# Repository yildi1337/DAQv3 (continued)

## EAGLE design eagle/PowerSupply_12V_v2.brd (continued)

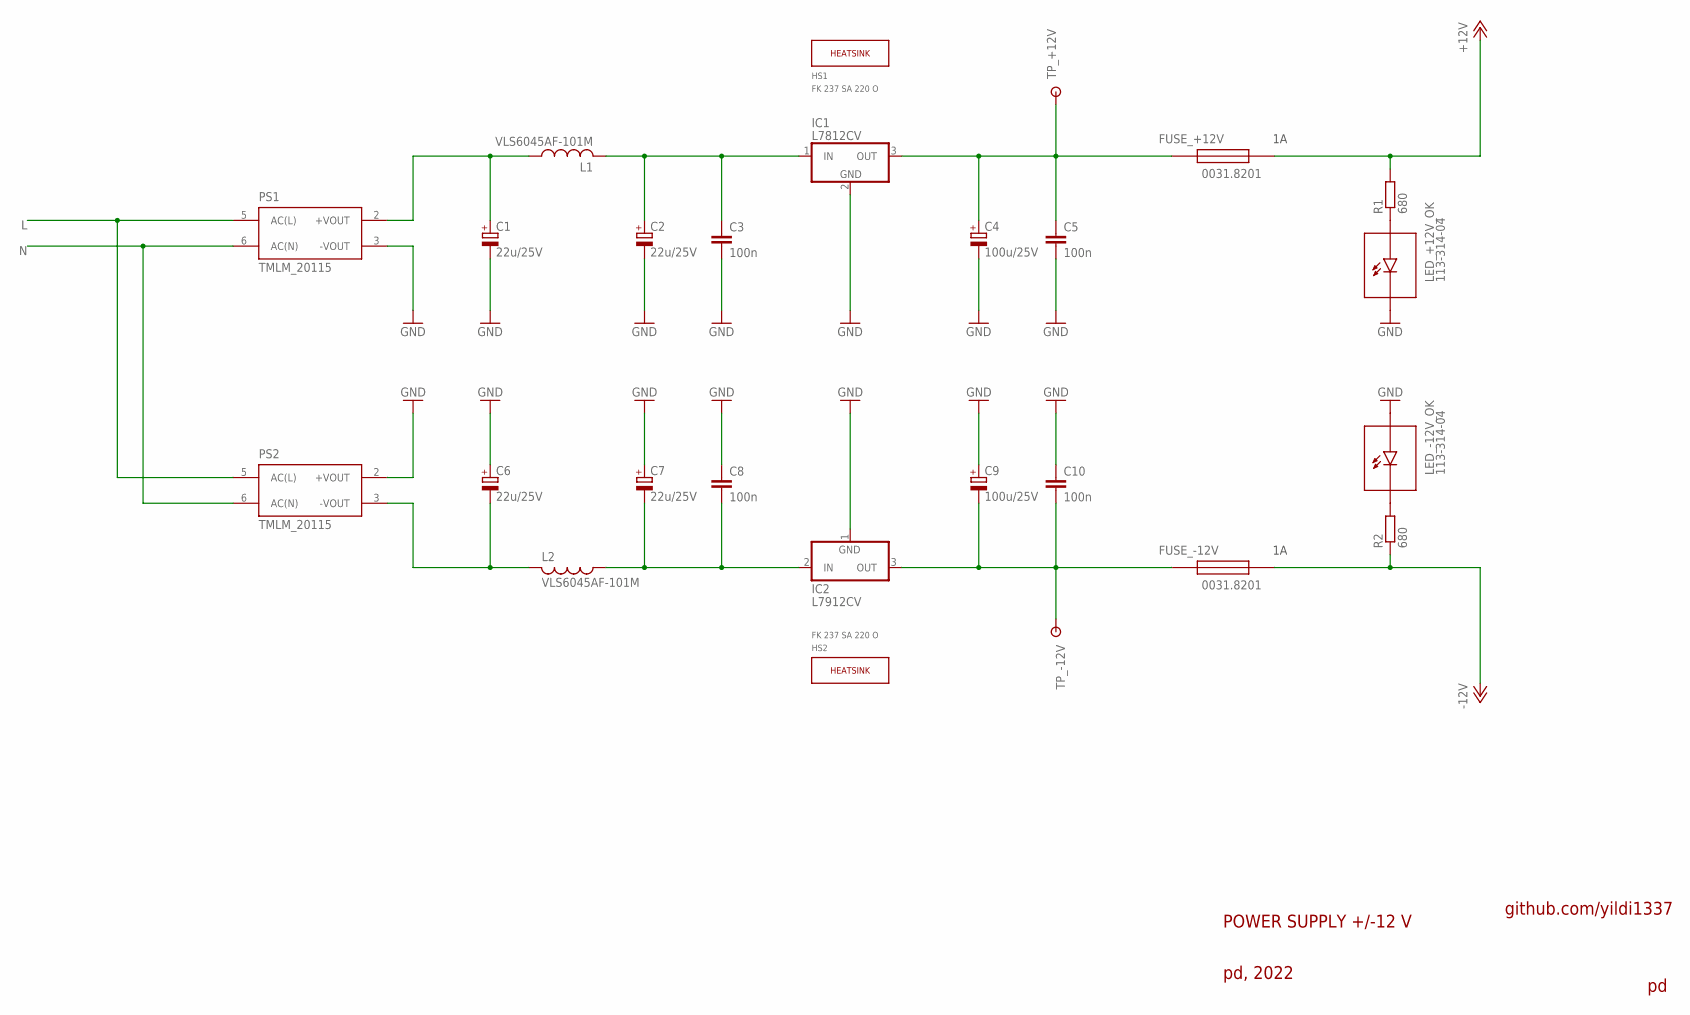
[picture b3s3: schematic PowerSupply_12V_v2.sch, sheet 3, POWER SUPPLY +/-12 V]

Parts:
C1, C2, C6, C7: 22u/25V; 153CLV-0505
C3, C5, C8, C10: 100n; C0603
C4, C9: 100u/25V; 153CLV-0810
FUSE_+12V: 0031.8201
FUSE_-12V: 0031.8201
HS1, HS2: FK 237 SA 220 O; FK_237_SA_220_O
IC1: L7812CV
IC2: L7912CV
L1, L2: VLS6045AF-101M
LED_+12V_OK: 113-314-04
LED_-12V_OK: 113-314-04
PS1, PS2: TMLM_20115; TMLM_201XX
R1, R2: 680; R0603
TP_+12V: RSPRO-1MM-TERMINAL-POST-2622034
TP_-12V: RSPRO-1MM-TERMINAL-POST-2622034

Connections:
+12V: FUSE_+12V.2, R1.2; also elsewhere on the board
-12V: FUSE_-12V.2, R2.1; also elsewhere on the board
GND: C1.-, C2.-, C3.2, C4.-, C5.2, C6.+, C7.+, C8.1, C9.+, C10.1, IC1.2 (GND), IC2.1 (GND), LED_+12V_OK.- (C), LED_-12V_OK.+ (A), PS1.3 (-VOUT), PS2.2 (+VOUT); also elsewhere on the board
L: PS1.5 (AC(L)), PS2.5 (AC(L)); also elsewhere on the board
N: PS1.6 (AC(N)), PS2.6 (AC(N)); also elsewhere on the board
unnamed: C7.-, C8.2, IC2.2 (IN), L2.1
unnamed: LED_-12V_OK.- (C), R2.2
unnamed: C9.-, C10.2, FUSE_-12V.1, IC2.3 (OUT), TP_-12V.P$1
unnamed: C1.+, L1.1, PS1.2 (+VOUT)
unnamed: C6.-, L2.2, PS2.3 (-VOUT)
unnamed: LED_+12V_OK.+ (A), R1.1
unnamed: C4.+, C5.1, FUSE_+12V.1, IC1.3 (OUT), TP_+12V.P$1
unnamed: C2.+, C3.1, IC1.1 (IN), L1.2

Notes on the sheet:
POWER SUPPLY +/-12 V
pd, 2022
github.com/yildi1337

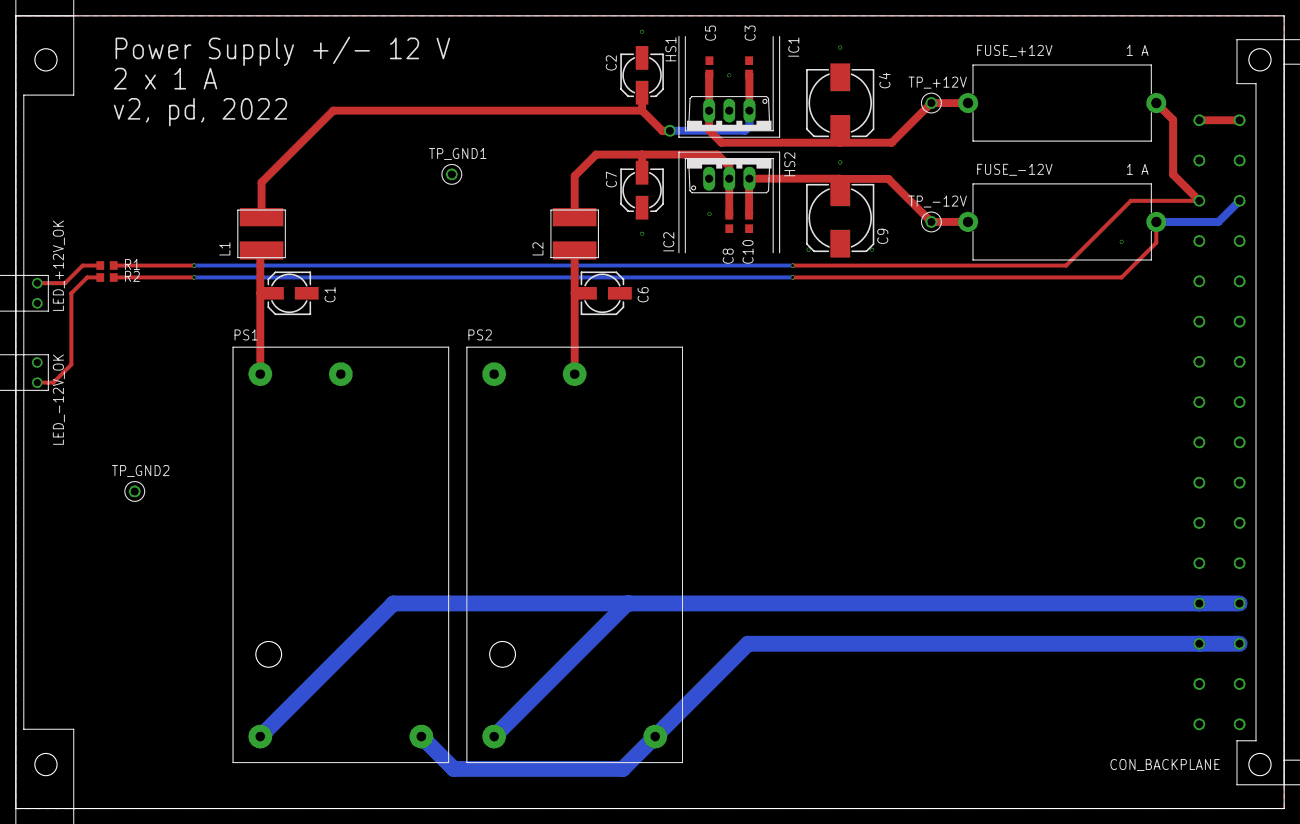
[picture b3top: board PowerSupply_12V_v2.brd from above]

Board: 2 copper layers, 160.0 x 100.0 mm, 30 parts (0 on the bottom side), 14 nets.

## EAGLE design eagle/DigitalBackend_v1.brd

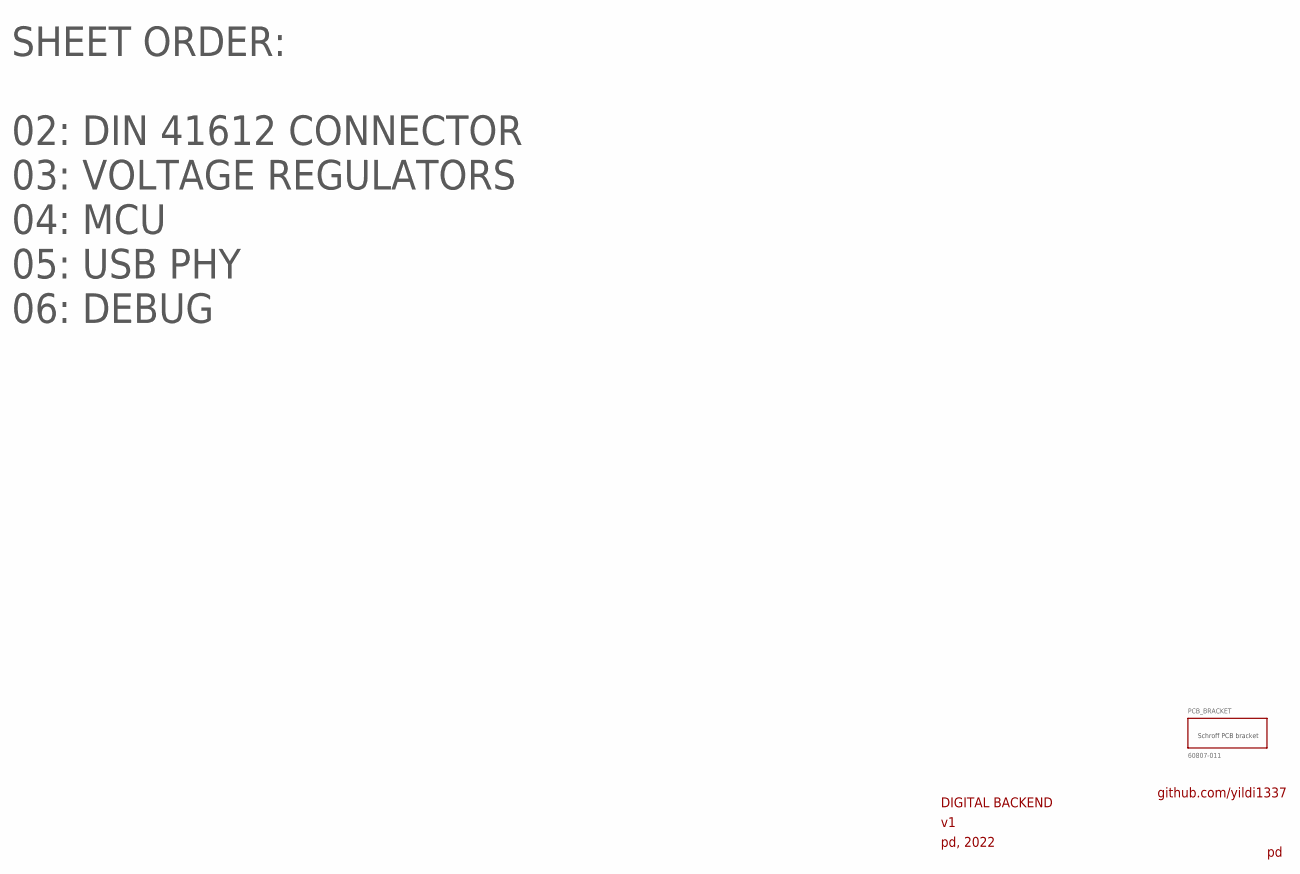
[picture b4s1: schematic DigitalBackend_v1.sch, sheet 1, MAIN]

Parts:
PCB_BRACKET: 60807-011

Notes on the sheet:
DIGITAL BACKEND
pd, 2022
github.com/yildi1337
SHEET ORDER: 02: DIN 41612 CONNECTOR 03: VOLTAGE REGULATORS 04: MCU 05: USB PHY 06: DEBUG

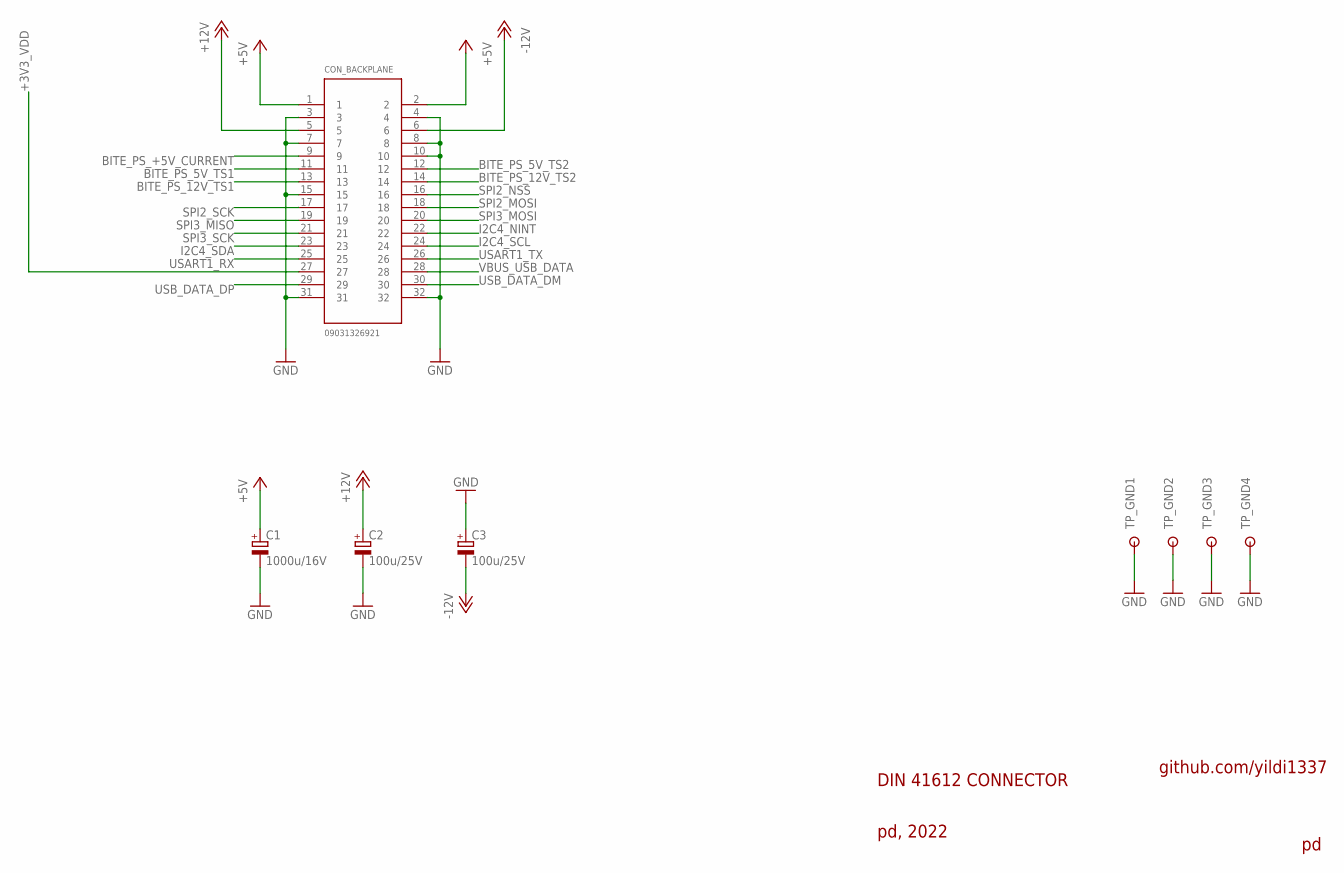
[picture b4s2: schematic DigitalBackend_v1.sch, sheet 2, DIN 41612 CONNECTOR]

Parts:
C1: 1000u/16V; 153CLV-1010
C2, C3: 100u/25V; 153CLV-0810
CON_BACKPLANE: 09031326921
TP_GND1, TP_GND2, TP_GND3, TP_GND4: RSPRO-1MM-TERMINAL-POST-2622034

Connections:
+3V3_VDD: CON_BACKPLANE.27; also elsewhere on the board
+5V: C1.+, CON_BACKPLANE.1, CON_BACKPLANE.2; also elsewhere on the board
+12V: C2.+, CON_BACKPLANE.5; also elsewhere on the board
-12V: C3.-, CON_BACKPLANE.6
BITE_PS_5V_TS1: CON_BACKPLANE.11
BITE_PS_5V_TS2: CON_BACKPLANE.12
BITE_PS_12V_TS1: CON_BACKPLANE.13
BITE_PS_12V_TS2: CON_BACKPLANE.14
BITE_PS_+5V_CURRENT: CON_BACKPLANE.9
GND: C1.-, C2.-, C3.+, CON_BACKPLANE.3, CON_BACKPLANE.4, CON_BACKPLANE.7, CON_BACKPLANE.8, CON_BACKPLANE.10, CON_BACKPLANE.15, CON_BACKPLANE.31, CON_BACKPLANE.32, TP_GND1.P$1, TP_GND2.P$1, TP_GND3.P$1, TP_GND4.P$1; also elsewhere on the board
I2C4_NINT: CON_BACKPLANE.22; also elsewhere on the board
I2C4_SCL: CON_BACKPLANE.24; also elsewhere on the board
I2C4_SDA: CON_BACKPLANE.23; also elsewhere on the board
SPI2_MOSI: CON_BACKPLANE.18; also elsewhere on the board
SPI2_NSS: CON_BACKPLANE.16; also elsewhere on the board
SPI2_SCK: CON_BACKPLANE.17; also elsewhere on the board
SPI3_MISO: CON_BACKPLANE.19; also elsewhere on the board
SPI3_MOSI: CON_BACKPLANE.20; also elsewhere on the board
SPI3_SCK: CON_BACKPLANE.21; also elsewhere on the board
USART1_RX: CON_BACKPLANE.25; also elsewhere on the board
USART1_TX: CON_BACKPLANE.26; also elsewhere on the board
USB_DATA_DM: CON_BACKPLANE.30; also elsewhere on the board
USB_DATA_DP: CON_BACKPLANE.29; also elsewhere on the board
VBUS_USB_DATA: CON_BACKPLANE.28; also elsewhere on the board

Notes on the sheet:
DIN 41612 CONNECTOR
pd, 2022
github.com/yildi1337

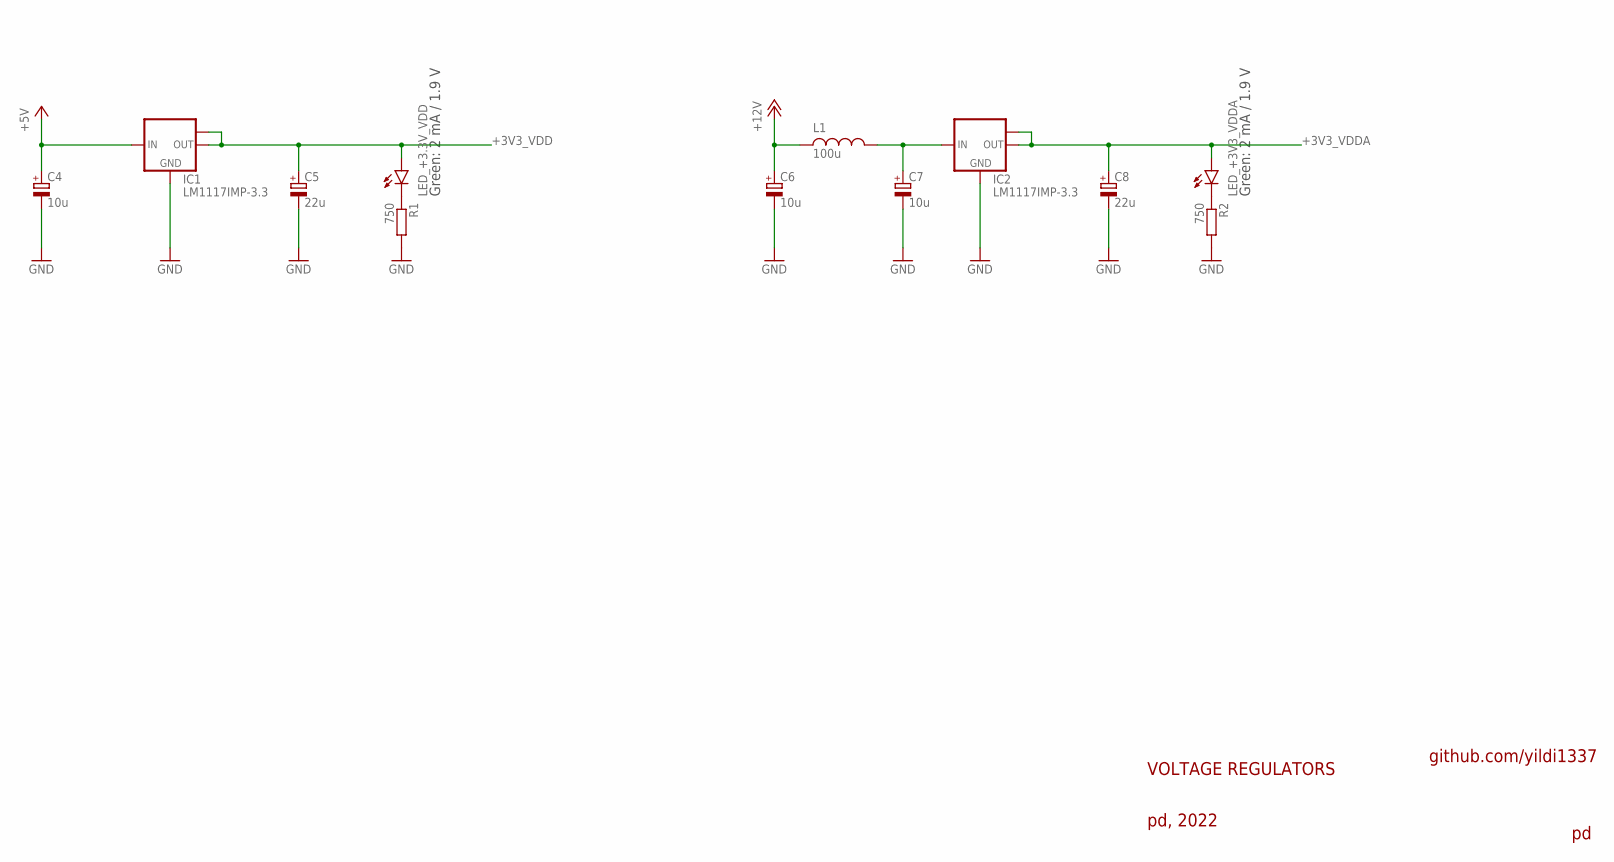
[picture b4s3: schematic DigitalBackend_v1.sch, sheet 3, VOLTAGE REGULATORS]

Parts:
C4, C6, C7: 10u; CT3216
C5, C8: 22u; CT6032
IC1, IC2: LM1117IMP-3.3; SOT223
L1: 100u; VLS6045AF-101M
LED_+3.3V_VDD, LED_+3V3_VDDA: LEDCHIP-LED0603; CHIP-LED0603
R1, R2: 750; R0603

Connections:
+3V3_VDD: C5.+, IC1.2 (OUT), IC1.TAB (OUT1), LED_+3.3V_VDD.A; also elsewhere on the board
+3V3_VDDA: C8.+, IC2.2 (OUT), IC2.TAB (OUT1), LED_+3V3_VDDA.A; also elsewhere on the board
+5V: C4.+, IC1.3 (IN); also elsewhere on the board
+12V: C6.+, L1.1; also elsewhere on the board
GND: C4.-, C5.-, C6.-, C7.-, C8.-, IC1.1 (GND), IC2.1 (GND), R1.2, R2.2; also elsewhere on the board
unnamed: C7.+, IC2.3 (IN), L1.2
unnamed: LED_+3.3V_VDD.C, R1.1
unnamed: LED_+3V3_VDDA.C, R2.1

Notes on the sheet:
VOLTAGE REGULATORS
pd, 2022
github.com/yildi1337
Green: 2 mA / 1.9 V

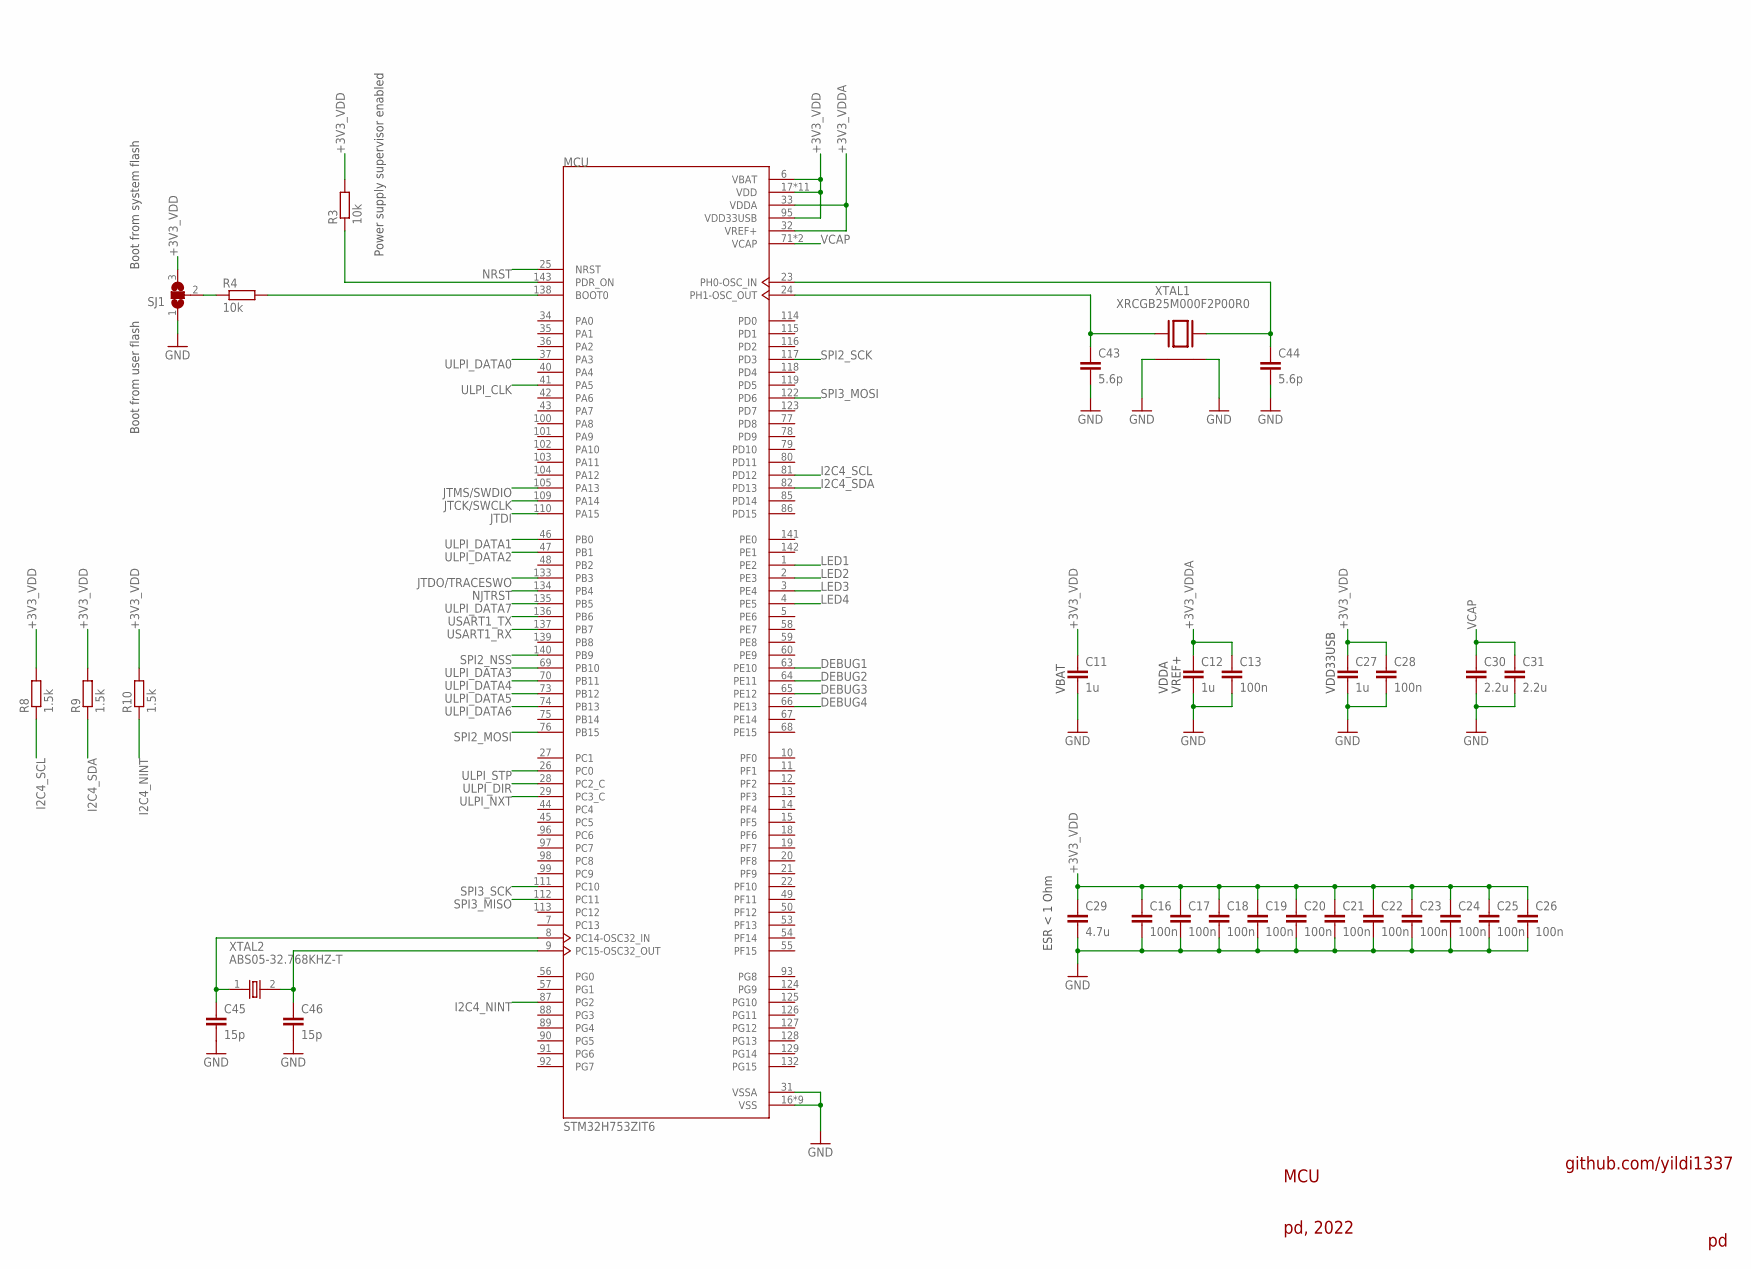
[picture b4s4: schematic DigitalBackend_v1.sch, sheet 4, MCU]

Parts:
C11, C12, C27: 1u; C0603
C13, C16, C17, C18, C19, C20, C21, C22, C23, C24, C25, C26, C28: 100n; C0603
C29: 4.7u; C0603
C30, C31: 2.2u; C0603
C43, C44: 5.6p; C0603
C45, C46: 15p; C0603
MCU: STM32H753ZIT6; LQFP144
R3, R4: 10k; R0603
R8, R9, R10: 1.5k; R0603
SJ1: SJ2W; SJ_2
XTAL1: XRCGB25M000F2P00R0
XTAL2: ABS05-32.768KHZ-T

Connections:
+3V3_VDD: C11.1, C16.1, C17.1, C18.1, C19.1, C20.1, C21.1, C22.1, C23.1, C24.1, C25.1, C26.1, C27.1, C28.1, C29.1, MCU.6 (VBAT), MCU.17 (VDD), MCU.30 (VDD), MCU.39 (VDD), MCU.52 (VDD), MCU.62 (VDD), MCU.72 (VDD), MCU.84 (VDD), MCU.95 (VDD33USB), MCU.108 (VDD), MCU.121 (VDD), MCU.131 (VDD), MCU.144 (VDD), R3.2, R8.2, R9.2, R10.2, SJ1.3; also elsewhere on the board
+3V3_VDDA: C12.1, C13.1, MCU.32 (VREF+), MCU.33 (VDDA); also elsewhere on the board
DEBUG1: MCU.63 (PE10); also elsewhere on the board
DEBUG2: MCU.64 (PE11); also elsewhere on the board
DEBUG3: MCU.65 (PE12); also elsewhere on the board
DEBUG4: MCU.66 (PE13); also elsewhere on the board
GND: C11.2, C12.2, C13.2, C16.2, C17.2, C18.2, C19.2, C20.2, C21.2, C22.2, C23.2, C24.2, C25.2, C26.2, C27.2, C28.2, C29.2, C30.2, C31.2, C43.2, C44.2, C45.2, C46.2, MCU.16 (VSS), MCU.31 (VSSA), MCU.38 (VSS), MCU.51 (VSS), MCU.61 (VSS), MCU.83 (VSS), MCU.94 (VSS), MCU.107 (VSS), MCU.120 (VSS), MCU.130 (VSS), SJ1.1, XTAL1.2 (GND2), XTAL1.4 (GND4); also elsewhere on the board
I2C4_NINT: MCU.87 (PG2), R10.1; also elsewhere on the board
I2C4_SCL: MCU.81 (PD12), R8.1; also elsewhere on the board
I2C4_SDA: MCU.82 (PD13), R9.1; also elsewhere on the board
JTCK/SWCLK: MCU.109 (PA14); also elsewhere on the board
JTDI: MCU.110 (PA15); also elsewhere on the board
JTDO/TRACESWO: MCU.133 (PB3); also elsewhere on the board
JTMS/SWDIO: MCU.105 (PA13); also elsewhere on the board
LED1: MCU.1 (PE2); also elsewhere on the board
LED2: MCU.2 (PE3); also elsewhere on the board
LED3: MCU.3 (PE4); also elsewhere on the board
LED4: MCU.4 (PE5); also elsewhere on the board
unnamed: MCU.143 (PDR_ON), R3.1
unnamed: MCU.138 (BOOT0), R4.2
unnamed: R4.1, SJ1.2
unnamed: C45.1, MCU.8 (PC14-OSC32_IN), XTAL2.1
unnamed: C44.1, MCU.23 (PH0-OSC_IN), XTAL1.3
unnamed: C43.1, MCU.24 (PH1-OSC_OUT), XTAL1.1
unnamed: C46.1, MCU.9 (PC15-OSC32_OUT), XTAL2.2
NJTRST: MCU.134 (PB4); also elsewhere on the board
NRST: MCU.25 (NRST); also elsewhere on the board
SPI2_MOSI: MCU.76 (PB15); also elsewhere on the board
SPI2_NSS: MCU.140 (PB9); also elsewhere on the board
SPI2_SCK: MCU.117 (PD3); also elsewhere on the board
SPI3_MISO: MCU.112 (PC11); also elsewhere on the board
SPI3_MOSI: MCU.122 (PD6); also elsewhere on the board
SPI3_SCK: MCU.111 (PC10); also elsewhere on the board
ULPI_CLK: MCU.41 (PA5); also elsewhere on the board
ULPI_DATA0: MCU.37 (PA3); also elsewhere on the board
ULPI_DATA1: MCU.46 (PB0); also elsewhere on the board
ULPI_DATA2: MCU.47 (PB1); also elsewhere on the board
ULPI_DATA3: MCU.69 (PB10); also elsewhere on the board
ULPI_DATA4: MCU.70 (PB11); also elsewhere on the board
ULPI_DATA5: MCU.73 (PB12); also elsewhere on the board
ULPI_DATA6: MCU.74 (PB13); also elsewhere on the board
ULPI_DATA7: MCU.135 (PB5); also elsewhere on the board
ULPI_DIR: MCU.28 (PC2_C); also elsewhere on the board
ULPI_NXT: MCU.29 (PC3_C); also elsewhere on the board
ULPI_STP: MCU.26 (PC0); also elsewhere on the board
USART1_RX: MCU.137 (PB7); also elsewhere on the board
USART1_TX: MCU.136 (PB6); also elsewhere on the board
VCAP: C30.1, C31.1, MCU.71 (VCAP), MCU.106 (VCAP)

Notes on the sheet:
MCU
pd, 2022
github.com/yildi1337
ESR < 1 Ohm
Power supply supervisor enabled
Boot from user flash
Boot from system flash
VBAT
VDDA
VDD33USB
VREF+

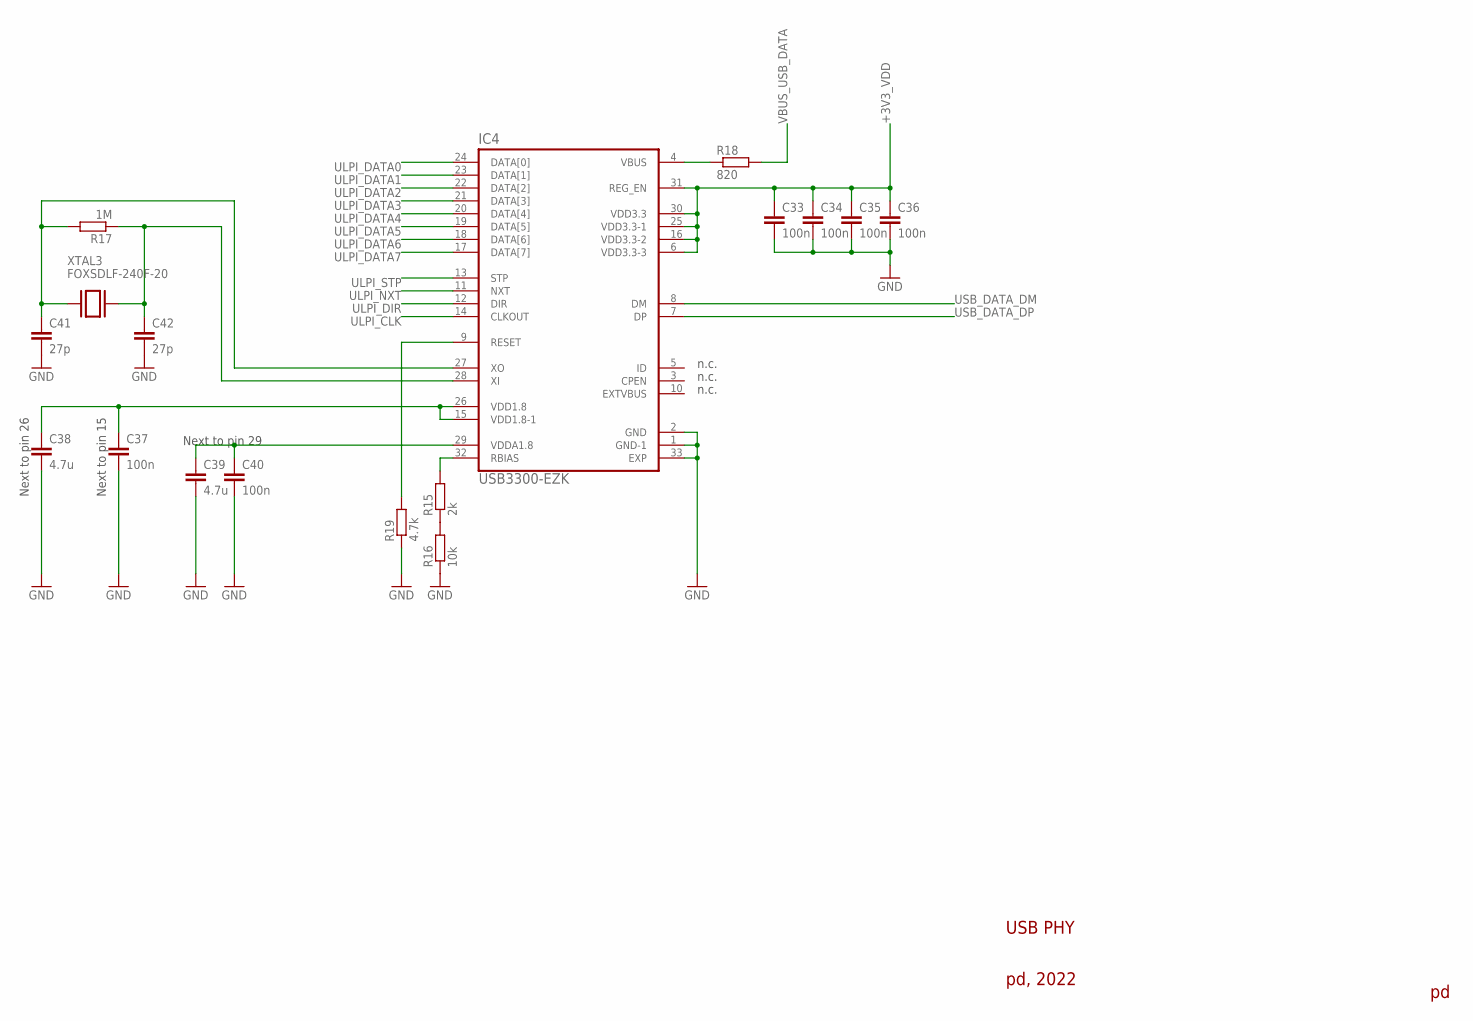
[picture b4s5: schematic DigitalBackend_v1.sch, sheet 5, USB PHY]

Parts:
C33, C34, C35, C36, C37, C40: 100n; C0603
C38, C39: 4.7u; C0603
C41, C42: 27p; C0603
IC4: USB3300-EZK
R15: 2k; R0603
R16: 10k; R0603
R17: 1M; R0603
R18: 820; R0603
R19: 4.7k; R0603
XTAL3: FOXSDLF-240F-20

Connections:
+3V3_VDD: C33.1, C34.1, C35.1, C36.1, IC4.6 (VDD3.3-3), IC4.16 (VDD3.3-2), IC4.25 (VDD3.3-1), IC4.30 (VDD3.3), IC4.31 (REG_EN); also elsewhere on the board
GND: C33.2, C34.2, C35.2, C36.2, C37.2, C38.2, C39.2, C40.2, C41.2, C42.2, IC4.1 (GND-1), IC4.2 (GND), IC4.33 (EXP), R16.1, R19.1; also elsewhere on the board
unnamed: C37.1, C38.1, IC4.15 (VDD1.8-1), IC4.26 (VDD1.8)
unnamed: C39.1, C40.1, IC4.29 (VDDA1.8)
unnamed: R15.1, R16.2
unnamed: IC4.32 (RBIAS), R15.2
unnamed: C41.1, IC4.27 (XO), R17.2, XTAL3.1
unnamed: C42.1, IC4.28 (XI), R17.1, XTAL3.2
unnamed: IC4.4 (VBUS), R18.1
unnamed: IC4.9 (RESET), R19.2
ULPI_CLK: IC4.14 (CLKOUT); also elsewhere on the board
ULPI_DATA0: IC4.24 (DATA[0]); also elsewhere on the board
ULPI_DATA1: IC4.23 (DATA[1]); also elsewhere on the board
ULPI_DATA2: IC4.22 (DATA[2]); also elsewhere on the board
ULPI_DATA3: IC4.21 (DATA[3]); also elsewhere on the board
ULPI_DATA4: IC4.20 (DATA[4]); also elsewhere on the board
ULPI_DATA5: IC4.19 (DATA[5]); also elsewhere on the board
ULPI_DATA6: IC4.18 (DATA[6]); also elsewhere on the board
ULPI_DATA7: IC4.17 (DATA[7]); also elsewhere on the board
ULPI_DIR: IC4.12 (DIR); also elsewhere on the board
ULPI_NXT: IC4.11 (NXT); also elsewhere on the board
ULPI_STP: IC4.13 (STP); also elsewhere on the board
USB_DATA_DM: IC4.8 (DM); also elsewhere on the board
USB_DATA_DP: IC4.7 (DP); also elsewhere on the board
VBUS_USB_DATA: R18.2; also elsewhere on the board

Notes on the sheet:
USB PHY
pd, 2022
n.c.
Next to pin 26
Next to pin 15
Next to pin 29

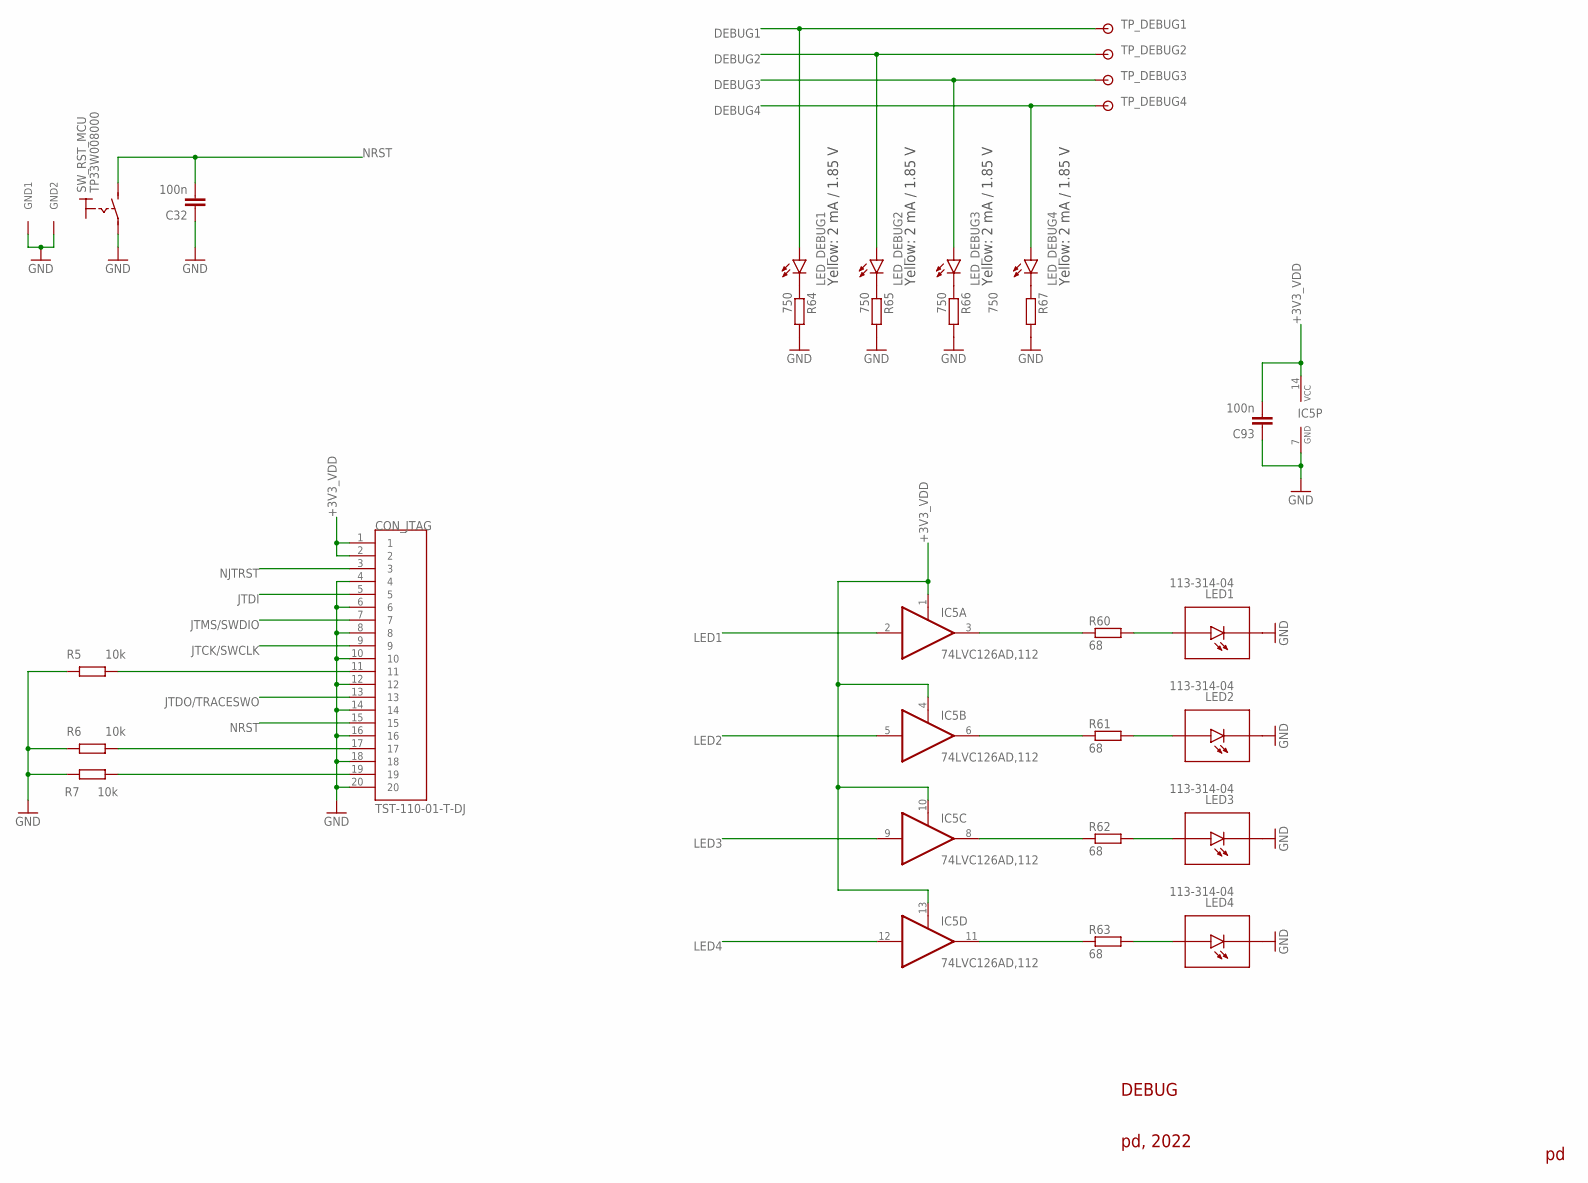
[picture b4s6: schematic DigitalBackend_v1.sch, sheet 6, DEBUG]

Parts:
C32, C93: 100n; C0603
CON_JTAG: TST-110-01-T-DJ; TST-110-01-T-D
IC5: 74LVC126AD,112; SO14
LED1, LED2, LED3, LED4: 113-314-04
LED_DEBUG1, LED_DEBUG2, LED_DEBUG3, LED_DEBUG4: LEDCHIP-LED0603; CHIP-LED0603
R5, R6, R7: 10k; R0603
R60, R61, R62, R63: 68; R0603
R64, R65, R66, R67: 750; R0603
SW_RST_MCU: TP33W008000
TP_DEBUG1, TP_DEBUG2, TP_DEBUG3, TP_DEBUG4: RSPRO-1MM-TERMINAL-POST-2622034

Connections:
+3V3_VDD: C93.2, CON_JTAG.1, CON_JTAG.2, IC5.1 (OE), IC5.4 (OE), IC5.10 (OE), IC5.13 (OE), IC5.14 (VCC); also elsewhere on the board
DEBUG1: LED_DEBUG1.A, TP_DEBUG1.P$1; also elsewhere on the board
DEBUG2: LED_DEBUG2.A, TP_DEBUG2.P$1; also elsewhere on the board
DEBUG3: LED_DEBUG3.A, TP_DEBUG3.P$1; also elsewhere on the board
DEBUG4: LED_DEBUG4.A, TP_DEBUG4.P$1; also elsewhere on the board
GND: C32.1, C93.1, CON_JTAG.4, CON_JTAG.6, CON_JTAG.8, CON_JTAG.10, CON_JTAG.12, CON_JTAG.14, CON_JTAG.16, CON_JTAG.18, CON_JTAG.20, IC5.7 (GND), LED1.- (C), LED2.- (C), LED3.- (C), LED4.- (C), R5.1, R6.1, R7.1, R64.2, R65.2, R66.2, R67.2, SW_RST_MCU.GND1, SW_RST_MCU.GND2, SW_RST_MCU.P1; also elsewhere on the board
JTCK/SWCLK: CON_JTAG.9; also elsewhere on the board
JTDI: CON_JTAG.5; also elsewhere on the board
JTDO/TRACESWO: CON_JTAG.13; also elsewhere on the board
JTMS/SWDIO: CON_JTAG.7; also elsewhere on the board
LED1: IC5.2 (I); also elsewhere on the board
LED2: IC5.5 (I); also elsewhere on the board
LED3: IC5.9 (I); also elsewhere on the board
LED4: IC5.12 (I); also elsewhere on the board
unnamed: CON_JTAG.19, R7.2
unnamed: CON_JTAG.17, R6.2
unnamed: CON_JTAG.11, R5.2
unnamed: LED1.+ (A), R60.2
unnamed: LED2.+ (A), R61.2
unnamed: LED3.+ (A), R62.2
unnamed: LED4.+ (A), R63.2
unnamed: IC5.3 (O), R60.1
unnamed: IC5.6 (O), R61.1
unnamed: IC5.8 (O), R62.1
unnamed: IC5.11 (O), R63.1
unnamed: LED_DEBUG1.C, R64.1
unnamed: LED_DEBUG2.C, R65.1
unnamed: LED_DEBUG3.C, R66.1
unnamed: LED_DEBUG4.C, R67.1
NJTRST: CON_JTAG.3; also elsewhere on the board
NRST: C32.2, CON_JTAG.15, SW_RST_MCU.P3; also elsewhere on the board

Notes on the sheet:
DEBUG
pd, 2022
Yellow: 2 mA / 1.85 V

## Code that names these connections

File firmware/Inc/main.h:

/*
 *******************************************************************************
 * File:			main.h
 * Date:			2022-04-10
 * Author:			Phillip Durdaut
 * Summary:			Main include file with main program definitions
 * Notes:			-
 *******************************************************************************
 */

/* Define to prevent recursive inclusion -------------------------------------*/
#ifndef __MAIN_H
#define __MAIN_H

/* Includes ------------------------------------------------------------------*/
#include <stdio.h>
#include <stdlib.h>
#include <string.h>
#include <stdbool.h>
#include <stdint.h>
#include <float.h>
#include <ctype.h>

#include "stm32h7xx.h"
#include "stm32h7xx_hal.h"
#include "stm32h7xx_it.h"

#include "tca9534a.h"

/* Public defines ------------------------------------------------------------*/

/* ADC */
#define MAIN_ADC_SAMPLES_PER_SECOND						256e3
#define MAIN_ADC_SAMPLES_PER_MILLI_SECOND				256
#define MAIN_ADC_NUM_CHANNELS							4
#define MAIN_ADC_BYTES_PER_SAMPLE_PER_CHANNEL			4
#define MAIN_ADC_BYTES_PER_SAMPLE						(MAIN_ADC_NUM_CHANNELS * MAIN_ADC_BYTES_PER_SAMPLE_PER_CHANNEL)
#define MAIN_ADC_BYTES_PER_SECOND_PER_CHANNEL			(MAIN_ADC_BYTES_PER_SAMPLE_PER_CHANNEL * MAIN_ADC_SAMPLES_PER_SECOND)
#define MAIN_ADC_BYTES_PER_SECOND						(MAIN_ADC_NUM_CHANNELS * MAIN_ADC_BYTES_PER_SAMPLE_PER_CHANNEL * MAIN_ADC_SAMPLES_PER_SECOND)
#define MAIN_ADC_BYTES_PER_MILLI_SECOND_PER_CHANNEL		(MAIN_ADC_BYTES_PER_SAMPLE_PER_CHANNEL * MAIN_ADC_SAMPLES_PER_MILLI_SECOND)
#define MAIN_ADC_BYTES_PER_MILLI_SECOND					(MAIN_ADC_NUM_CHANNELS * MAIN_ADC_BYTES_PER_SAMPLE_PER_CHANNEL * MAIN_ADC_SAMPLES_PER_MILLI_SECOND)
#define MAIN_ADC_CLIPPING_VALUE							(4194304+100000)	/* slightly above 2.5 V */

/* USB */
#define MAIN_USB_VENDOR_ID								0x1337
#define MAIN_USB_PRODUCT_ID								0x0011
#define MAIN_USB_LANG_ID_STRING_US		 				0x0409
#define MAIN_USB_LANG_ID_STRING_DE		 				0x0407
#define MAIN_USB_LANG_ID_STRING							MAIN_USB_LANG_ID_STRING_US
#define MAIN_USB_MANUFACTURER_STRING	  				"pd"
#define MAIN_USB_PRODUCT_STRING							"DAQ v3"
#define MAIN_USB_SERIAL_STRING	 						"0000"
#define MAIN_USB_CONFIGURATION_STRING  					"DAQ v3 Config"
#define MAIN_USB_INTERFACE_STRING	  					"DAQ v3 Interface"
#define MAIN_USB_DEVICE_VERSION							0x0100

/* Interrupt priorities */
#define IRQ_UART1_PREEMPT_PRIORITY				2
#define IRQ_UART1_SUB_PRIORITY					2
#define IRQ_DMA1_STREAM0_PREEMPT_PRIORITY		10
#define IRQ_DMA1_STREAM0_SUB_PRIORITY			10
#define IRQ_OTG_HS_EP1_OUT_PREEMPT_PRIORITY		5
#define IRQ_OTG_HS_EP1_OUT_SUB_PRIORITY			5
#define IRQ_OTG_HS_EP1_IN_PREEMPT_PRIORITY		5
#define IRQ_OTG_HS_EP1_IN_SUB_PRIORITY			5
#define IRQ_OTG_HS_PREEMPT_PRIORITY				5
#define IRQ_OTG_HS_SUB_PRIORITY					5

/* Pins and ports */
#define LED_1_Pin 											GPIO_PIN_2
#define LED_1_Port 											GPIOE
#define LED_2_Pin 											GPIO_PIN_3
#define LED_2_Port 											GPIOE
#define LED_3_Pin 											GPIO_PIN_4
#define LED_3_Port 											GPIOE
#define LED_4_Pin 											GPIO_PIN_5
#define LED_4_Port 											GPIOE

#define DEBUG_1_Pin 										GPIO_PIN_10
#define DEBUG_1_Port 										GPIOE
#define DEBUG_2_Pin 										GPIO_PIN_11
#define DEBUG_2_Port 										GPIOE
#define DEBUG_3_Pin 										GPIO_PIN_12
#define DEBUG_3_Port 										GPIOE
#define DEBUG_4_Pin 										GPIO_PIN_13
#define DEBUG_4_Port 										GPIOE

#define UART1_TX_Pin										GPIO_PIN_6
#define UART1_TX_Port 										GPIOB
#define UART1_TX_AF 										GPIO_AF7_USART1
#define UART1_RX_Pin										GPIO_PIN_7
#define UART1_RX_Port 										GPIOB
#define UART1_RX_AF 										GPIO_AF7_USART1

#define SPI2_NSS_Pin 										GPIO_PIN_9
#define SPI2_NSS_Port 										GPIOB
#define SPI2_NSS_AF											GPIO_AF5_SPI2
#define SPI2_SCK_Pin 										GPIO_PIN_3
#define SPI2_SCK_Port 										GPIOD
#define SPI2_SCK_AF											GPIO_AF5_SPI2
#define SPI2_MOSI_Pin 										GPIO_PIN_15
#define SPI2_MOSI_Port 										GPIOB
#define SPI2_MOSI_AF										GPIO_AF5_SPI2

#define SPI3_SCK_Pin 										GPIO_PIN_10
#define SPI3_SCK_Port 										GPIOC
#define SPI3_SCK_AF											GPIO_AF6_SPI3
#define SPI3_MISO_Pin 										GPIO_PIN_11
#define SPI3_MISO_Port 										GPIOC
#define SPI3_MISO_AF										GPIO_AF6_SPI3
#define SPI3_MOSI_Pin 										GPIO_PIN_6
#define SPI3_MOSI_Port 										GPIOD
#define SPI3_MOSI_AF										GPIO_AF5_SPI3

#define USB_OTG_HS_ULPI_STP_Pin 							GPIO_PIN_0
#define USB_OTG_HS_ULPI_STP_Port 							GPIOC
#define USB_OTG_HS_ULPI_STP_AF								GPIO_AF10_OTG2_HS
#define USB_OTG_HS_ULPI_DIR_Pin 							GPIO_PIN_2
#define USB_OTG_HS_ULPI_DIR_Port 							GPIOC
#define USB_OTG_HS_ULPI_DIR_AF								GPIO_AF10_OTG2_HS
#define USB_OTG_HS_ULPI_NXT_Pin 							GPIO_PIN_3
#define USB_OTG_HS_ULPI_NXT_Port 							GPIOC
#define USB_OTG_HS_ULPI_NXT_AF								GPIO_AF10_OTG2_HS
#define USB_OTG_HS_ULPI_CK_Pin 								GPIO_PIN_5
#define USB_OTG_HS_ULPI_CK_Port 							GPIOA
#define USB_OTG_HS_ULPI_CK_AF								GPIO_AF10_OTG2_HS
#define USB_OTG_HS_ULPI_D0_Pin 								GPIO_PIN_3
#define USB_OTG_HS_ULPI_D0_Port 							GPIOA
#define USB_OTG_HS_ULPI_D0_AF								GPIO_AF10_OTG2_HS
#define USB_OTG_HS_ULPI_D1_Pin 								GPIO_PIN_0
#define USB_OTG_HS_ULPI_D1_Port 							GPIOB
#define USB_OTG_HS_ULPI_D1_AF								GPIO_AF10_OTG2_HS
#define USB_OTG_HS_ULPI_D2_Pin 								GPIO_PIN_1
#define USB_OTG_HS_ULPI_D2_Port 							GPIOB
#define USB_OTG_HS_ULPI_D2_AF								GPIO_AF10_OTG2_HS
#define USB_OTG_HS_ULPI_D3_Pin 								GPIO_PIN_10
#define USB_OTG_HS_ULPI_D3_Port 							GPIOB
#define USB_OTG_HS_ULPI_D3_AF								GPIO_AF10_OTG2_HS
#define USB_OTG_HS_ULPI_D4_Pin 								GPIO_PIN_11
#define USB_OTG_HS_ULPI_D4_Port 							GPIOB
#define USB_OTG_HS_ULPI_D4_AF								GPIO_AF10_OTG2_HS
#define USB_OTG_HS_ULPI_D5_Pin 								GPIO_PIN_12
#define USB_OTG_HS_ULPI_D5_Port 							GPIOB
#define USB_OTG_HS_ULPI_D5_AF								GPIO_AF10_OTG2_HS
#define USB_OTG_HS_ULPI_D6_Pin 								GPIO_PIN_13
#define USB_OTG_HS_ULPI_D6_Port 							GPIOB
#define USB_OTG_HS_ULPI_D6_AF								GPIO_AF10_OTG2_HS
#define USB_OTG_HS_ULPI_D7_Pin 								GPIO_PIN_5
#define USB_OTG_HS_ULPI_D7_Port 							GPIOB
#define USB_OTG_HS_ULPI_D7_AF								GPIO_AF10_OTG2_HS

#define I2C4_SCL_Port										GPIOD
#define I2C4_SCL_Pin										GPIO_PIN_12
#define I2C4_SCL_AF											GPIO_AF4_I2C4
#define I2C4_SDA_Port										GPIOD
#define I2C4_SDA_Pin										GPIO_PIN_13
#define I2C4_SDA_AF											GPIO_AF4_I2C4

/* I/O expander */
#define ADC_NRESET_DEVICE									TCA9534A_DEVICE_ACNV
#define ADC_NRESET_PIN										TCA9534A_PIN_0
#define ADC_SPI_NCS_DEVICE									TCA9534A_DEVICE_ACNV
#define ADC_SPI_NCS_PIN										TCA9534A_PIN_1
#define RD_NCS_DEVICE										TCA9534A_DEVICE_ACNV
#define RD_NCS_PIN											TCA9534A_PIN_2
#define RD_NRESET_DEVICE									TCA9534A_DEVICE_ACNV
#define RD_NRESET_PIN										TCA9534A_PIN_3

/* Public macros -------------------------------------------------------------*/
/* Public typedefs -----------------------------------------------------------*/
typedef uint8_t flag_t;
typedef enum
{
	CHANNEL_1 = 0,
	CHANNEL_2 = 1,
	CHANNEL_NONE
} channel_t;

/* Public variables ----------------------------------------------------------*/
extern flag_t MAIN_MeasurementRunning;
extern flag_t MAIN_SamplesRequested;

/* Public function prototypes ------------------------------------------------*/
extern void Error_Handler(void);

#endif /* __MAIN_H */
